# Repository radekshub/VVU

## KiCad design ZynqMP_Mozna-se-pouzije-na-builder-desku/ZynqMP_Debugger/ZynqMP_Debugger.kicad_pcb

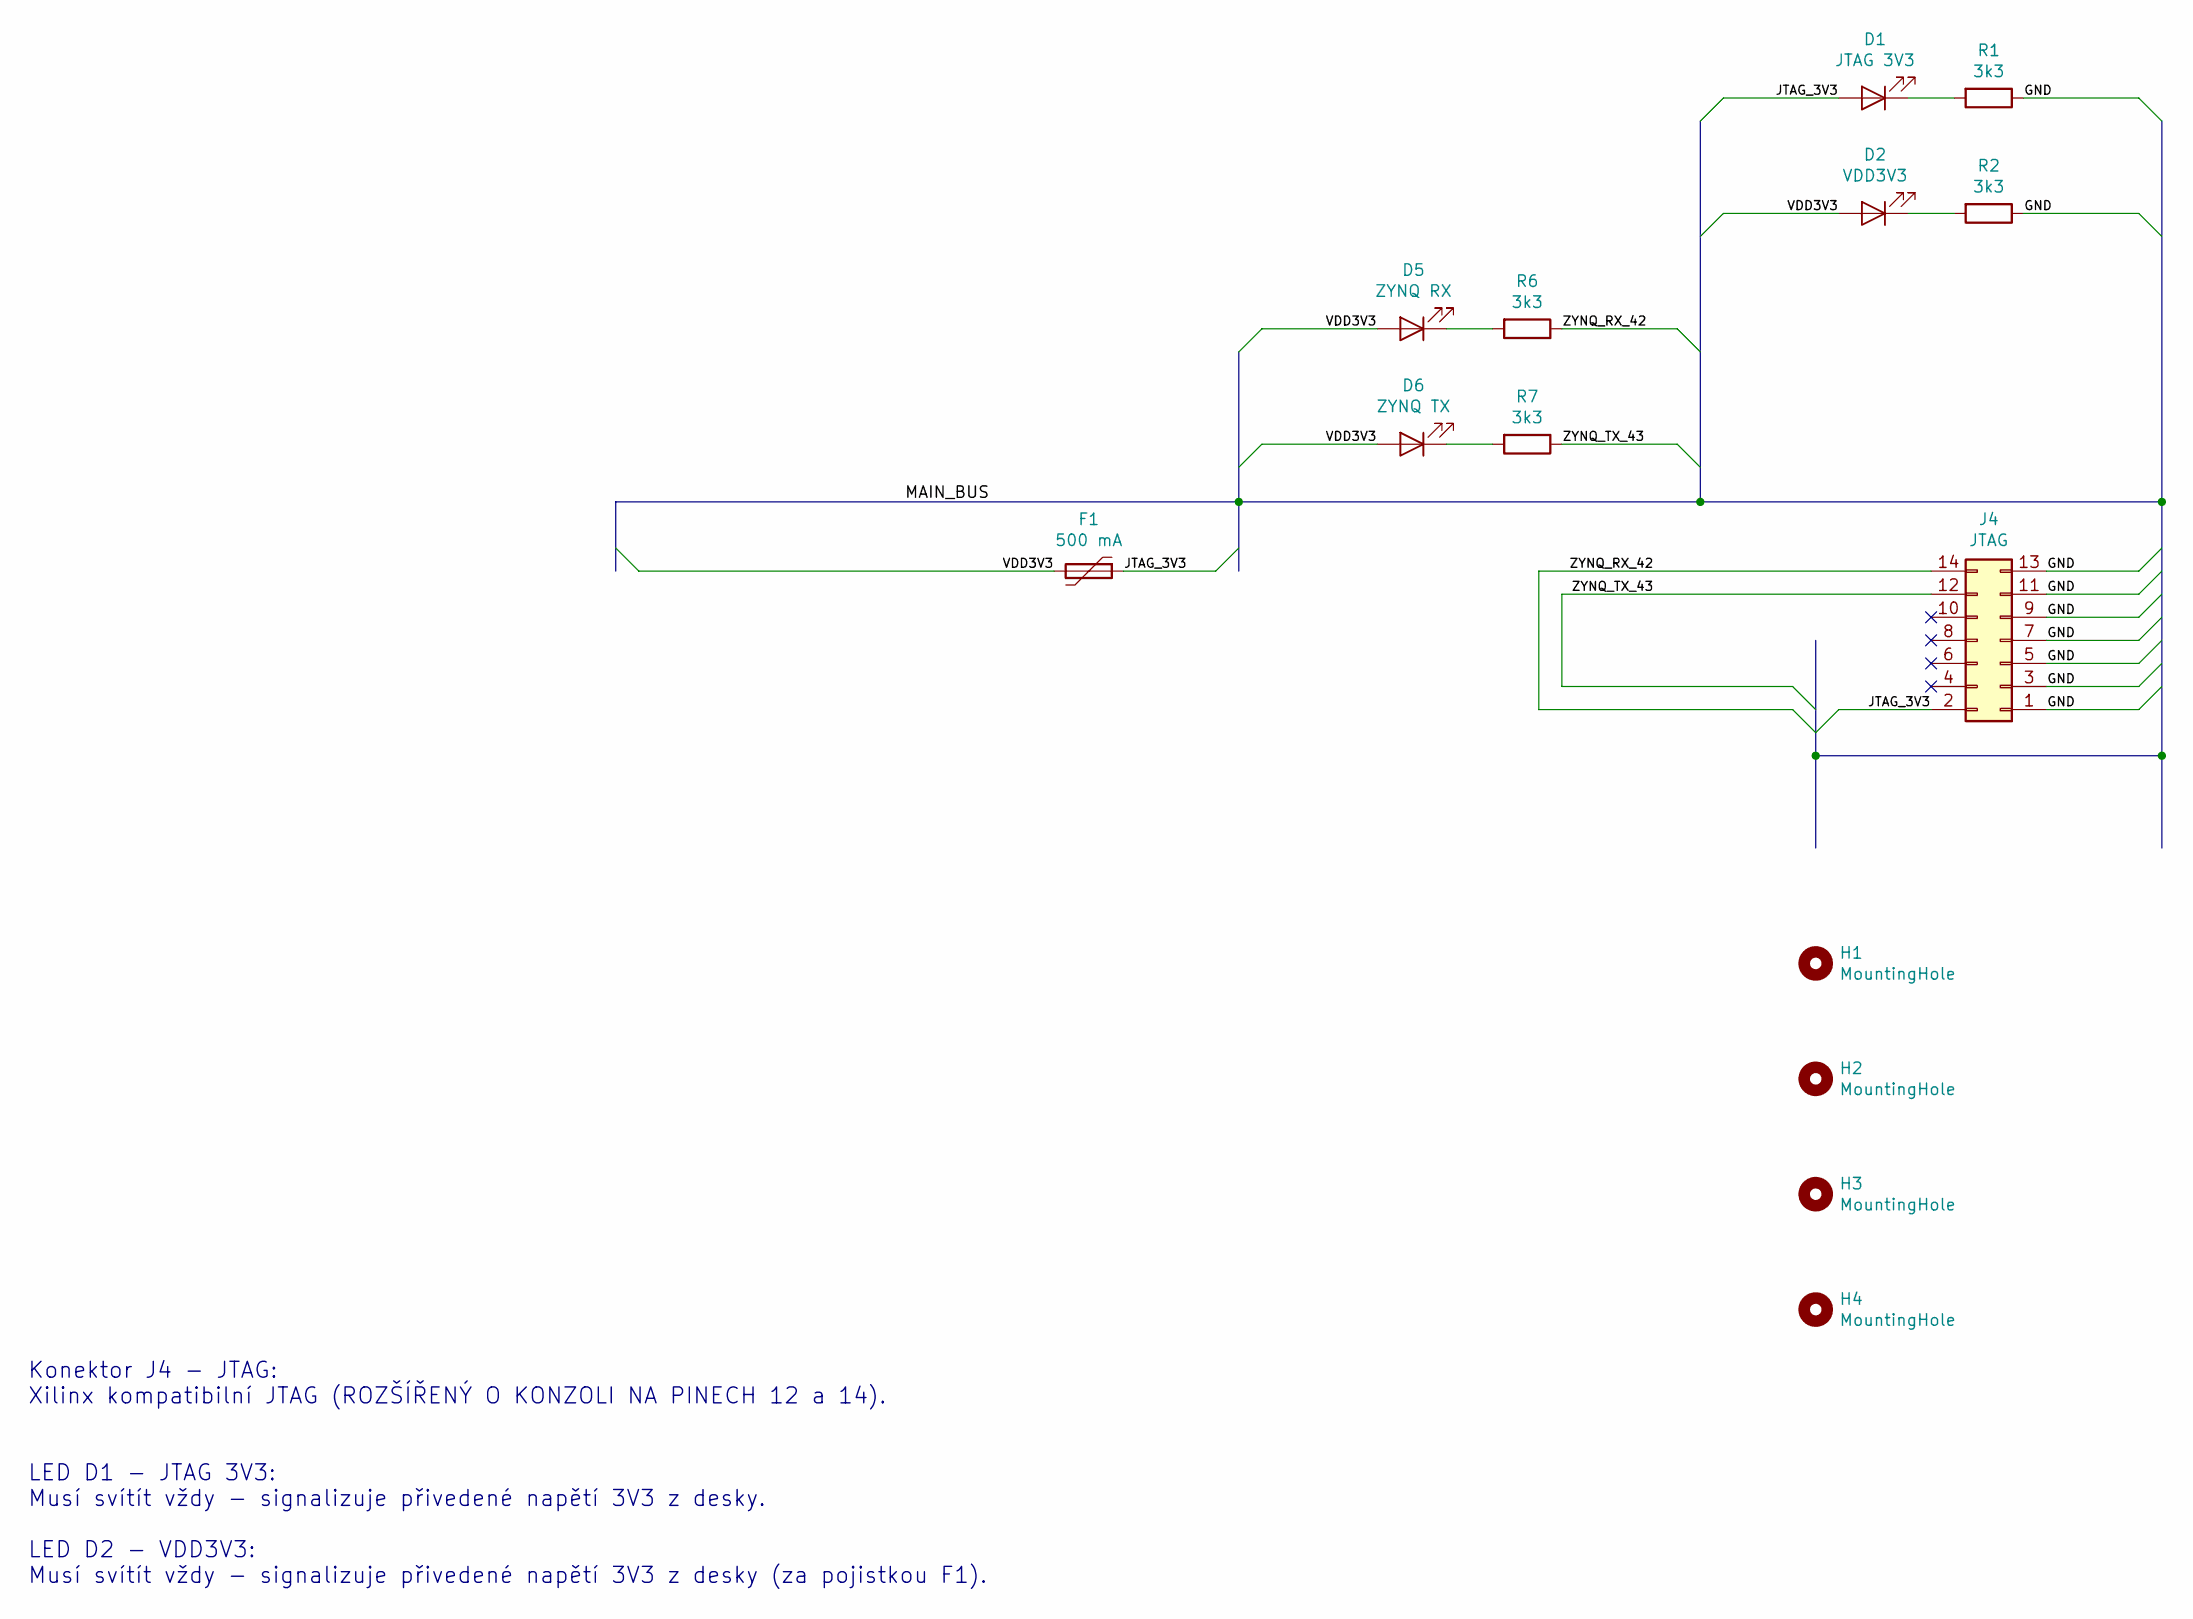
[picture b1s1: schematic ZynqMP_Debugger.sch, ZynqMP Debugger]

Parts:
D1: JTAG 3V3; LED_0805_2012Metric_Pad1.15x1.40mm_HandSolder
D2: VDD3V3; LED_0805_2012Metric_Pad1.15x1.40mm_HandSolder
D5: ZYNQ RX; LED_0805_2012Metric_Pad1.15x1.40mm_HandSolder
D6: ZYNQ TX; LED_0805_2012Metric_Pad1.15x1.40mm_HandSolder
F1: 500 mA; Fuse_1206_3216Metric_Pad1.42x1.75mm_HandSolder
H1, H2, H3, H4: MountingHole; MountingHole_4.3mm_M4_Pad_Via
J4: JTAG; JST_PHD_B14B-PHDSS_2x07_P2.00mm_Vertical
R1, R2, R6, R7: 3k3; R_0805_2012Metric_Pad1.15x1.40mm_HandSolder

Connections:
/GND: J4.1, J4.3, J4.5, J4.7, J4.9, J4.11, J4.13, R1.1, R2.1
/JTAG_3V3: D1.2 (A), F1.1, J4.2
/VDD3V3: D2.2 (A), D5.2 (A), D6.2 (A), F1.2
/ZYNQ_RX_42: J4.14, R6.1
/ZYNQ_TX_43: J4.12, R7.1
unnamed: D1.1 (K), R1.2
unnamed: D2.1 (K), R2.2
unnamed: D5.1 (K), R6.2
unnamed: D6.1 (K), R7.2

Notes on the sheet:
Konektor J4 - JTAG: Xilinx kompatibilní JTAG (ROZŠÍŘENÝ O KONZOLI NA PINECH 12 a 14). LED D1 - JTAG 3V3: Musí svítít vždy - signalizuje přivedené napětí 3V3 z desky. LED D2 - VDD3V3: Musí svítít vždy - signalizuje přivedené napětí 3V3 z desky (za pojistkou F1).

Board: 2 copper layers, 14 parts (0 on the bottom side), 9 nets, no tracks yet.

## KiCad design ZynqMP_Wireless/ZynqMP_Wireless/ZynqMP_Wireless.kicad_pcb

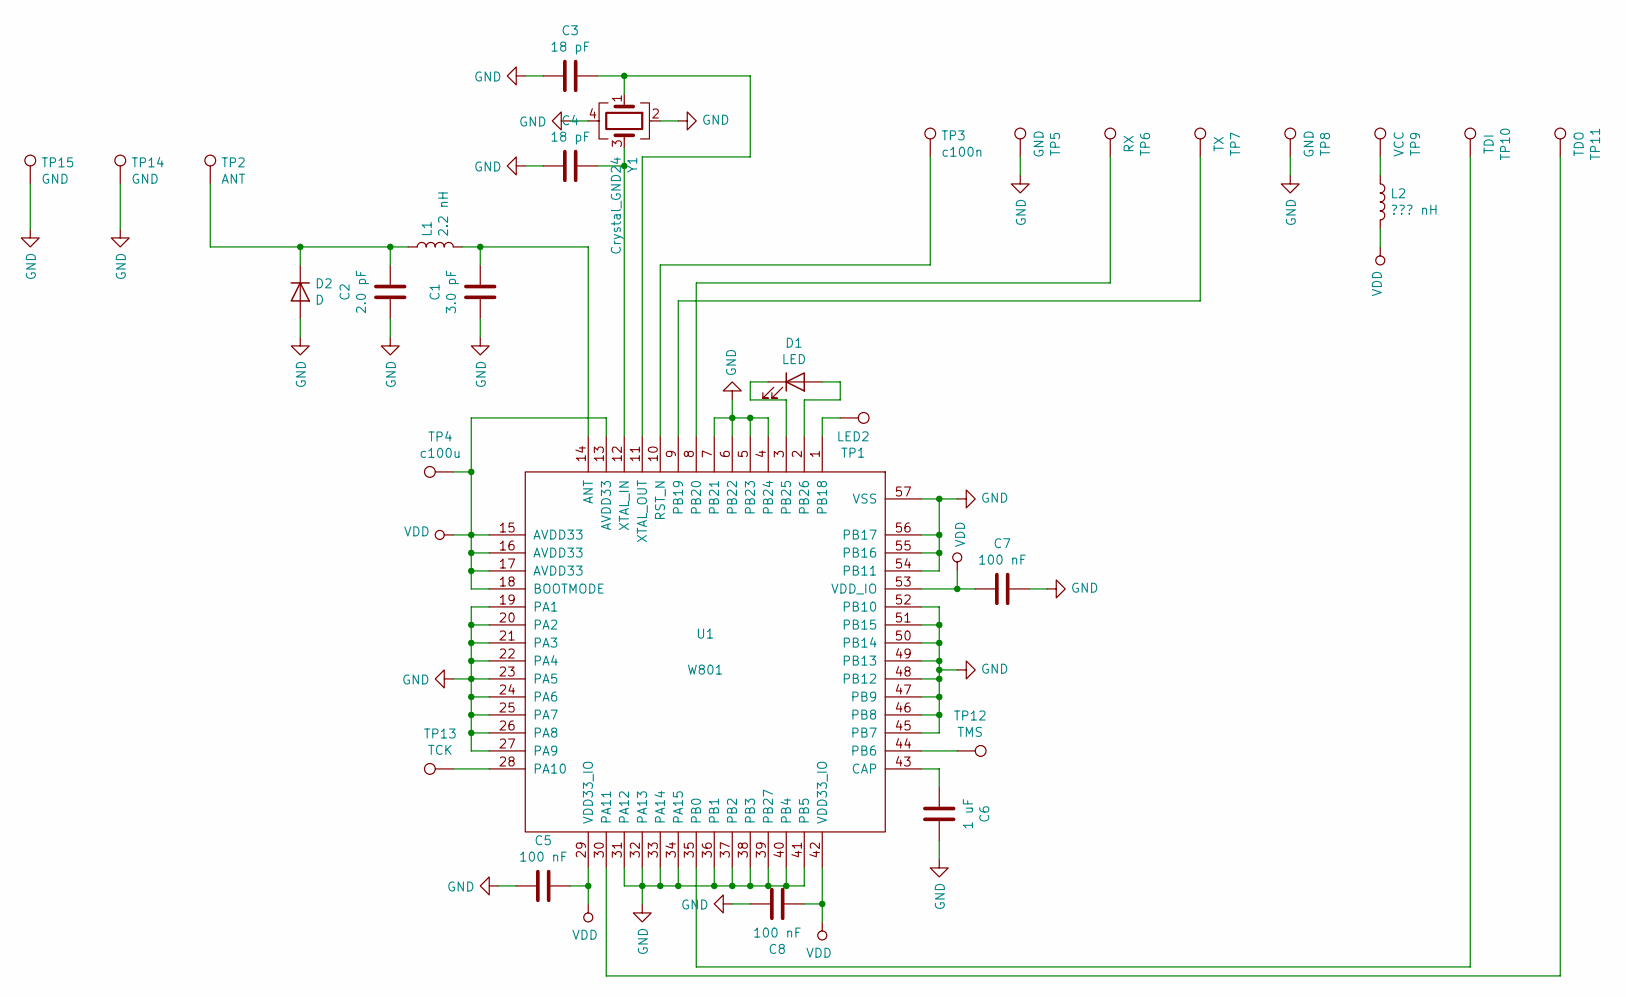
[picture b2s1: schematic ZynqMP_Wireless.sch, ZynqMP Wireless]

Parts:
C1: 3.0 pF; C_0201_0603Metric
C2: 2.0 pF; C_0201_0603Metric
C3, C4: 18 pF; C_0603_1608Metric
C5: 100 nF; C_0603_1608Metric_Pad1.05x0.95mm_HandSolder
C6: 1 uF; C_0603_1608Metric_Pad1.05x0.95mm_HandSolder
C7, C8: 100 nF; C_0603_1608Metric
D1: LED; LED_0603_1608Metric_Pad1.05x0.95mm_HandSolder
D2: D; D_0201_0603Metric
L1: 2.2 nH; L_0201_0603Metric
L2: ??? nH; L_0603_1608Metric_Pad1.05x0.95mm_HandSolder
TP1: LED2; TestPoint_Pad_1.0x1.0mm
TP2: ANT; MountingHole_4.3x6.2mm_M4_Pad
TP3: c100n; TestPoint_Pad_1.0x1.0mm
TP4: c100u; TestPoint_Pad_1.0x1.0mm
TP5, TP8: GND; TestPoint_Pad_1.0x1.0mm
TP6: RX; TestPoint_Pad_1.0x1.0mm
TP7: TX; TestPoint_Pad_1.0x1.0mm
TP9: VCC; TestPoint_Pad_1.0x1.0mm
TP10: TDI; TestPoint_Pad_1.0x1.0mm
TP11: TDO; TestPoint_Pad_1.0x1.0mm
TP12: TMS; TestPoint_Pad_1.0x1.0mm
TP13: TCK; TestPoint_Pad_1.0x1.0mm
TP14, TP15: GND; MountingHole_4.3x6.2mm_M4_Pad
U1: W801
Y1: Crystal_GND24; Crystal_SMD_3225-4Pin_3.2x2.5mm

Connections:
GND: C1.2, C2.2, C3.2, C4.2, C5.2, C6.1, C7.1, C8.1, D2.2 (A), TP5.1, TP8.1, TP14.1, TP15.1, U1.4 (PB24), U1.5 (PB23), U1.6 (PB22), U1.7 (PB21), U1.19 (PA1), U1.20 (PA2), U1.21 (PA3), U1.22 (PA4), U1.23 (PA5), U1.24 (PA6), U1.25 (PA7), U1.26 (PA8), U1.27 (PA9), U1.31 (PA12), U1.32 (PA13), U1.33 (PA14), U1.34 (PA15), U1.36 (PB1), U1.37 (PB2), U1.38 (PB3), U1.39 (PB27), U1.40 (PB4), U1.41 (PB5), U1.45 (PB7), U1.46 (PB8), U1.47 (PB9), U1.48 (PB12), U1.49 (PB13), U1.50 (PB14), U1.51 (PB15), U1.52 (PB10), U1.54 (PB11), U1.55 (PB16), U1.56 (PB17), U1.57 (VSS), Y1.2, Y1.4
unnamed: C1.1, L1.2, U1.14 (ANT)
unnamed: C2.1, D2.1 (K), L1.1, TP2.1
unnamed: C3.1, U1.11 (XTAL_OUT), Y1.1
unnamed: C4.1, U1.12 (XTAL_IN), Y1.3
unnamed: C6.2, U1.43 (CAP)
unnamed: D1.1 (K), U1.3 (PB25)
unnamed: D1.2 (A), U1.2 (PB26)
unnamed: L2.1, TP9.1
unnamed: TP1.1, U1.1 (PB18)
unnamed: TP3.1, U1.10 (RST_N)
unnamed: TP6.1, U1.8 (PB20)
unnamed: TP7.1, U1.9 (PB19)
unnamed: TP10.1, U1.35 (PB0)
unnamed: TP11.1, U1.30 (PA11)
unnamed: TP12.1, U1.44 (PB6)
unnamed: TP13.1, U1.28 (PA10)
VDD: C5.1, C7.2, C8.2, L2.2, TP4.1, U1.13 (AVDD33), U1.15 (AVDD33), U1.16 (AVDD33), U1.17 (AVDD33), U1.18 (BOOTMODE), U1.29 (VDD33_IO), U1.42 (VDD33_IO), U1.53 (VDD_IO)

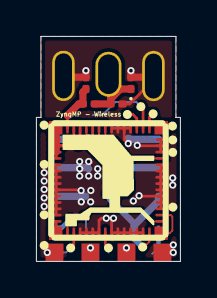
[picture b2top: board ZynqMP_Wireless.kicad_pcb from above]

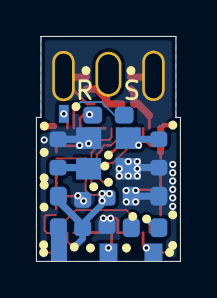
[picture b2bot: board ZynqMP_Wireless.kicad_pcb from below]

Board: 4 copper layers, 8.0 x 12.5 mm, 29 parts (13 on the bottom side), 18 nets.

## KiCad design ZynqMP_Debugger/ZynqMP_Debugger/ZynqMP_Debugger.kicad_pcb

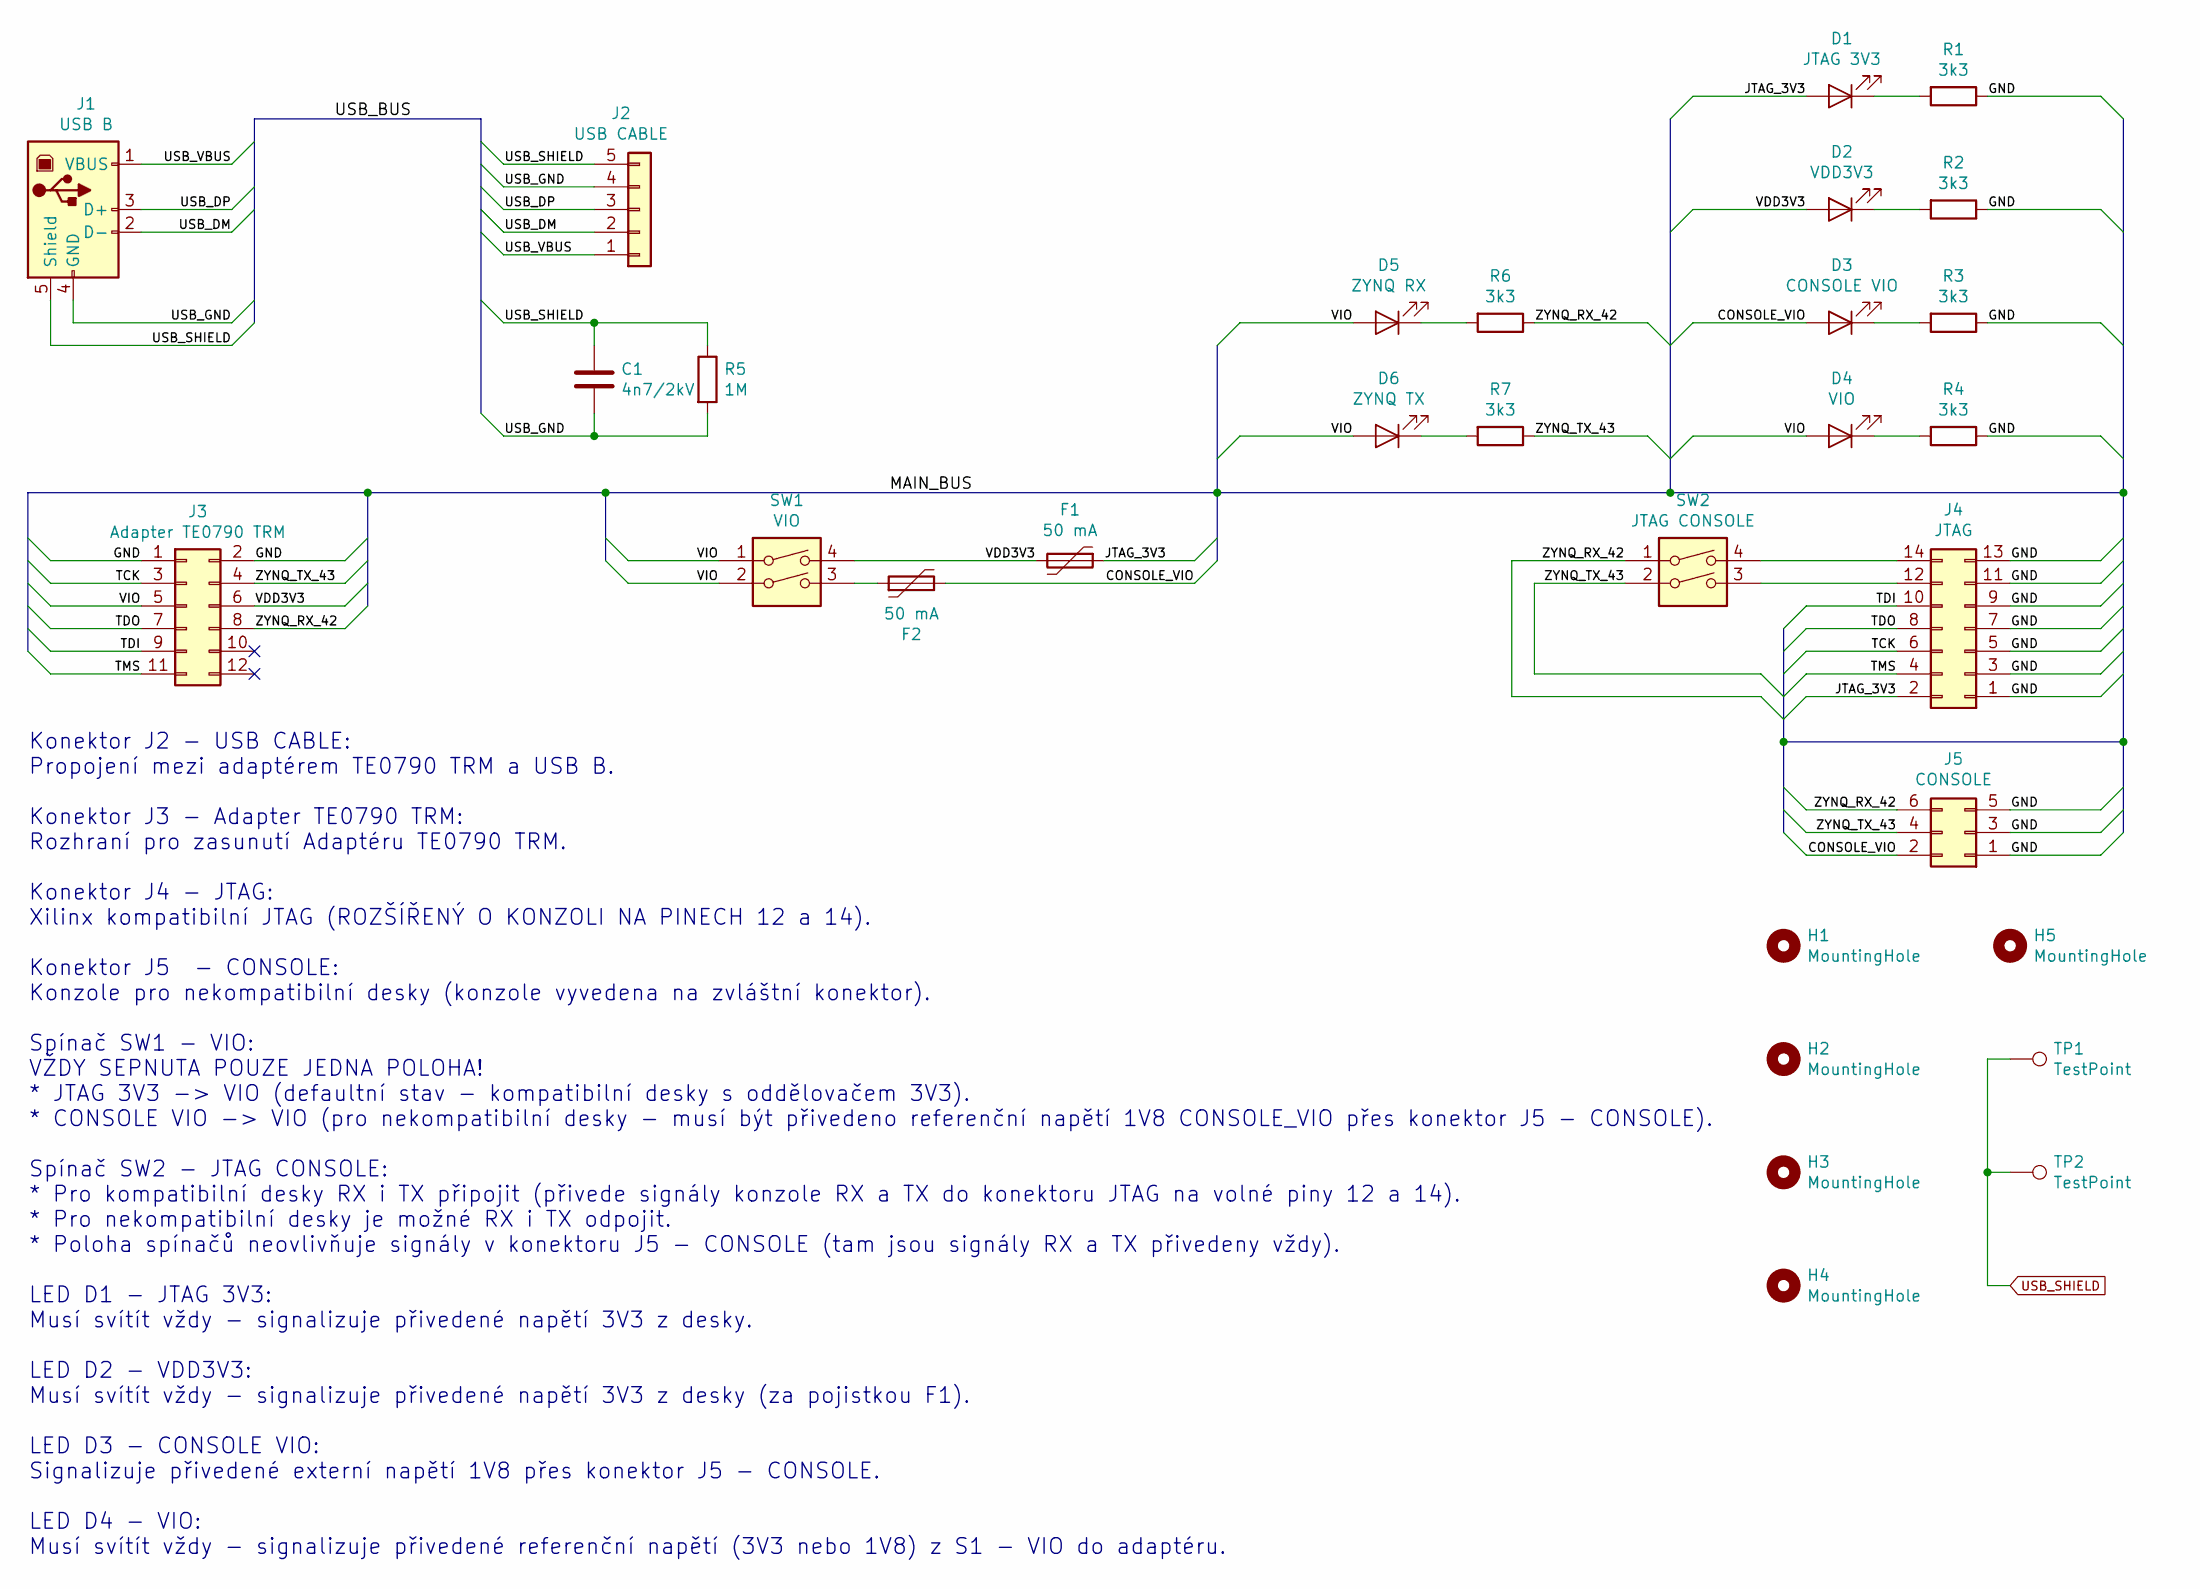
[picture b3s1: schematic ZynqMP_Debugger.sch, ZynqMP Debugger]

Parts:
C1: 4n7/2kV; C_Disc_D7.5mm_W2.5mm_P5.00mm
D1: JTAG 3V3; LED_0805_2012Metric_Pad1.15x1.40mm_HandSolder
D2: VDD3V3; LED_0805_2012Metric_Pad1.15x1.40mm_HandSolder
D3: CONSOLE VIO; LED_0805_2012Metric_Pad1.15x1.40mm_HandSolder
D4: VIO; LED_0805_2012Metric_Pad1.15x1.40mm_HandSolder
D5: ZYNQ RX; LED_0805_2012Metric_Pad1.15x1.40mm_HandSolder
D6: ZYNQ TX; LED_0805_2012Metric_Pad1.15x1.40mm_HandSolder
F1, F2: 50 mA; Fuse_1206_3216Metric_Pad1.42x1.75mm_HandSolder
H1, H2, H3, H4: MountingHole; MountingHole_4.3mm_M4_Pad_Via
H5: MountingHole; MountingHole_3mm_Pad_Via
J1: USB B; USB_B_OST_USB-B1HSxx_Horizontal
J2: USB CABLE; PinHeader_1x05_P2.54mm_Horizontal
J3: Adapter TE0790 TRM; PinHeader_2x06_P2.54mm_Vertical
J4: JTAG; JST_PHD_B14B-PHDSS_2x07_P2.00mm_Vertical
J5: CONSOLE; IDC-Header_2x03_P2.54mm_Vertical
R1, R2, R3, R4, R6, R7: 3k3; R_0805_2012Metric_Pad1.15x1.40mm_HandSolder
R5: 1M; R_0805_2012Metric_Pad1.15x1.40mm_HandSolder
SW1: VIO; SW_DIP_SPSTx02_Slide_9.78x7.26mm_W7.62mm_P2.54mm
SW2: JTAG CONSOLE; SW_DIP_SPSTx02_Slide_9.78x7.26mm_W7.62mm_P2.54mm
TP1, TP2: TestPoint; TestPoint_Bridge_Pitch5.08mm_Drill1.3mm

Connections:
/CONSOLE_VIO: D3.2 (A), F2.2, J5.2
/GND: J3.1, J3.2, J4.1, J4.3, J4.5, J4.7, J4.9, J4.11, J4.13, J5.1, J5.3, J5.5, R1.1, R2.1, R3.1, R4.1
/JTAG_3V3: D1.2 (A), F1.1, J4.2
/TCK: J3.3, J4.6
/TDI: J3.9, J4.10
/TDO: J3.7, J4.8
/TMS: J3.11, J4.4
/USB_DM: J1.2 (D-), J2.2
/USB_DP: J1.3 (D+), J2.3
/USB_GND: C1.2, J1.4 (GND), J2.4, R5.2
/USB_VBUS: J1.1 (VBUS), J2.1
/VDD3V3: D2.2 (A), F1.2, J3.6, SW1.4
/VIO: D4.2 (A), D5.2 (A), D6.2 (A), J3.5, SW1.1, SW1.2
/ZYNQ_RX_42: J3.8, J5.6, R6.1, SW2.1
/ZYNQ_TX_43: J3.4, J5.4, R7.1, SW2.2
unnamed: D1.1 (K), R1.2
unnamed: D2.1 (K), R2.2
unnamed: D3.1 (K), R3.2
unnamed: D4.1 (K), R4.2
unnamed: D5.1 (K), R6.2
unnamed: D6.1 (K), R7.2
unnamed: F2.1, SW1.3
unnamed: J4.12, SW2.3
unnamed: J4.14, SW2.4
USB_SHIELD: C1.1, J1.5 (Shield), J2.5, R5.1, TP1.1, TP2.1

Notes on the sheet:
Konektor J2 - USB CABLE: Propojení mezi adaptérem TE0790 TRM a USB B. Konektor J3 - Adapter TE0790 TRM: Rozhraní pro zasunutí Adaptéru TE0790 TRM. Konektor J4 - JTAG: Xilinx kompatibilní JTAG (ROZŠÍŘENÝ O KONZOLI NA PINECH 12 a 14). Konektor J5 - CONSOLE: Konzole pro nekompatibilní desky (konzole v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

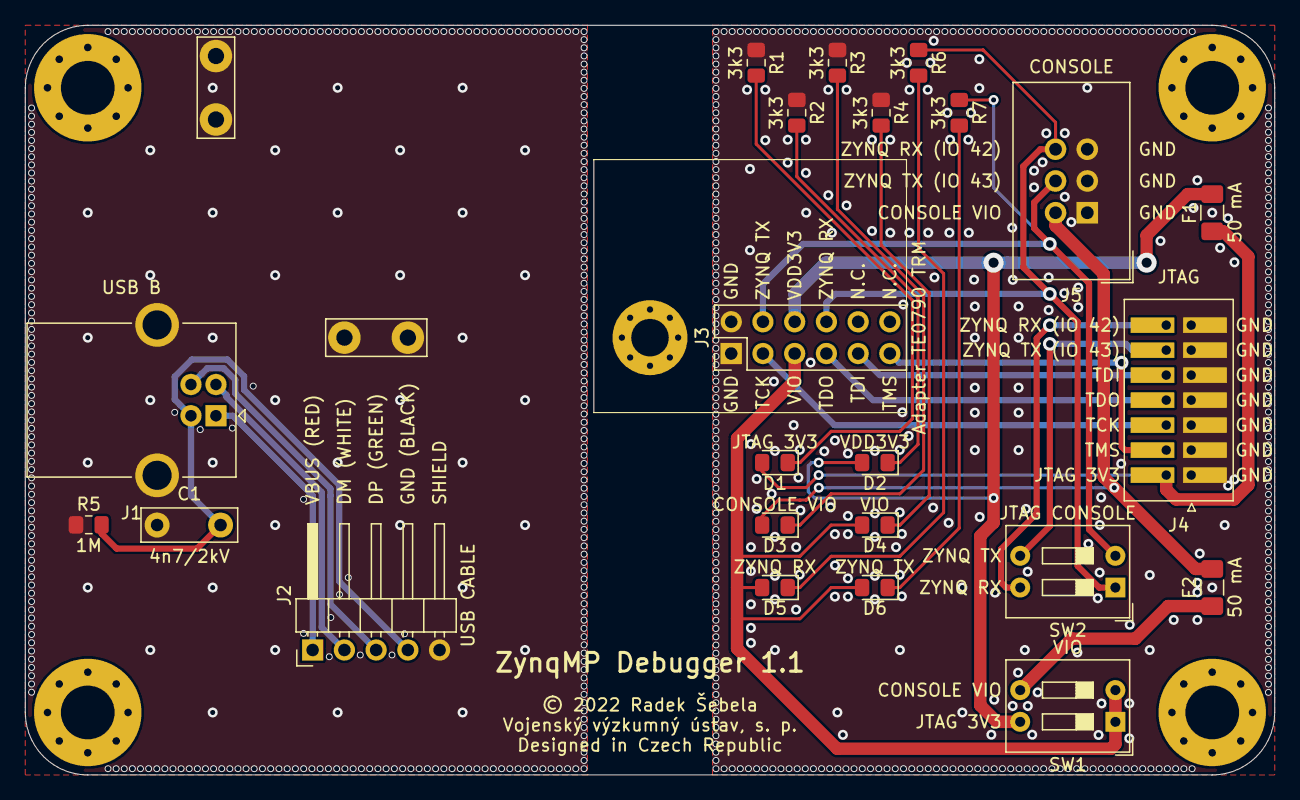
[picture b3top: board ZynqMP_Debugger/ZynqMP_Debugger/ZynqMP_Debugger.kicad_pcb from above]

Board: 2 copper layers, 100.0 x 60.0 mm, 30 parts (0 on the bottom side), 25 nets.

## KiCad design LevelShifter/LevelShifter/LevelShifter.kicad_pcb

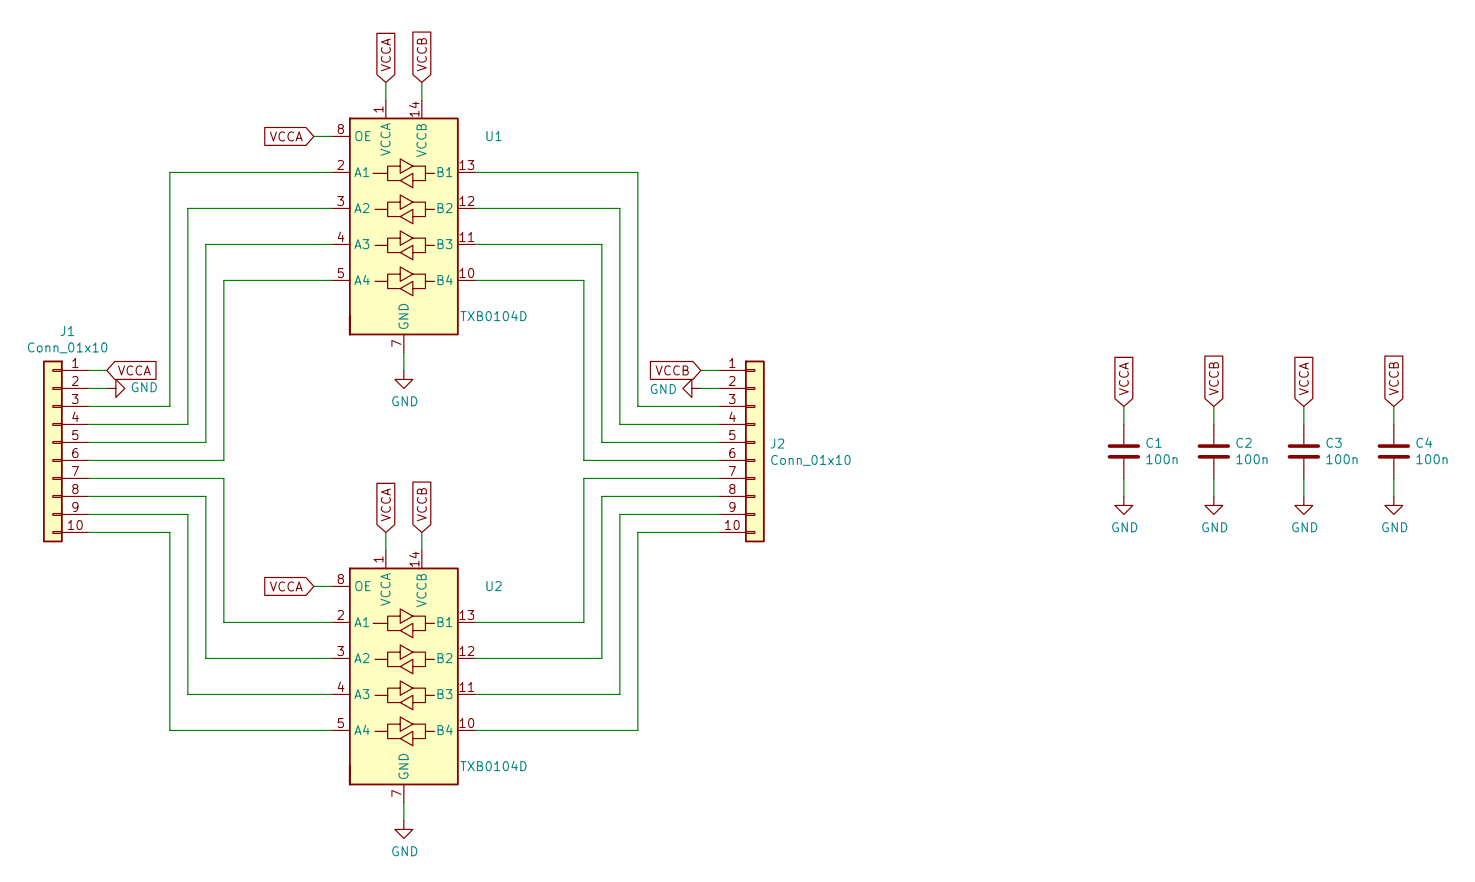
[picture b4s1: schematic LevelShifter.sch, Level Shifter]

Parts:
C1, C2, C3, C4: 100n; C_0805_2012Metric_Pad1.15x1.40mm_HandSolder
J1, J2: Conn_01x10; PinHeader_1x10_P2.00mm_Vertical
U1, U2: TXB0104D; SOIC-14_3.9x8.7mm_P1.27mm

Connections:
GND: C1.2, C2.2, C3.2, C4.2, J1.2, J2.2, U1.7 (GND), U2.7 (GND)
unnamed: J1.3, U1.2 (A1)
unnamed: J1.4, U1.3 (A2)
unnamed: J1.5, U1.4 (A3)
unnamed: J1.6, U1.5 (A4)
unnamed: J1.7, U2.2 (A1)
unnamed: J1.8, U2.3 (A2)
unnamed: J1.9, U2.4 (A3)
unnamed: J1.10, U2.5 (A4)
unnamed: J2.3, U1.13 (B1)
unnamed: J2.4, U1.12 (B2)
unnamed: J2.5, U1.11 (B3)
unnamed: J2.6, U1.10 (B4)
unnamed: J2.7, U2.13 (B1)
unnamed: J2.8, U2.12 (B2)
unnamed: J2.9, U2.11 (B3)
unnamed: J2.10, U2.10 (B4)
VCCA: C1.1, C3.1, J1.1, U1.1 (VCCA), U1.8 (OE), U2.1 (VCCA), U2.8 (OE)
VCCB: C2.1, C4.1, J2.1, U1.14 (VCCB), U2.14 (VCCB)

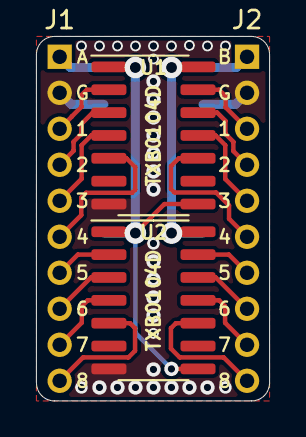
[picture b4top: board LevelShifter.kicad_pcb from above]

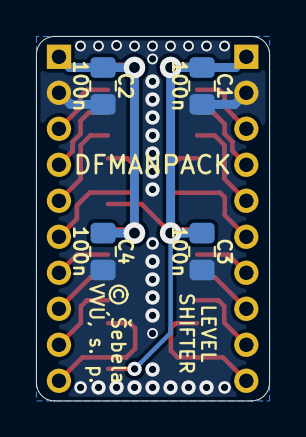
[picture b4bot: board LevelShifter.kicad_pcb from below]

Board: 2 copper layers, 13.0 x 20.2 mm, 8 parts (4 on the bottom side), 19 nets.

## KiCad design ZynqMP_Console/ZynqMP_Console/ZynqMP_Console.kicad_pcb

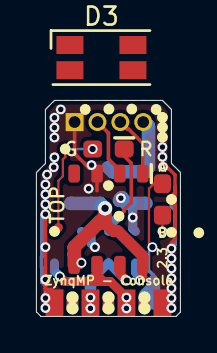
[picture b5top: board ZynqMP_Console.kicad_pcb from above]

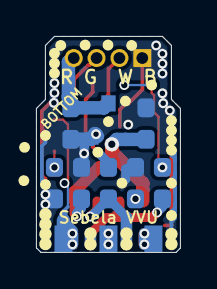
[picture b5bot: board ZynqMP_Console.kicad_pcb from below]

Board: 2 copper layers, 8.0 x 12.0 mm, 20 parts (11 on the bottom side), 11 nets.

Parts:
C1, C2: 1u; C_0603_1608Metric_Pad1.05x0.95mm_HandSolder
C3, C4: 100n; C_0603_1608Metric_Pad1.05x0.95mm_HandSolder
D1, D2: LED; LED_0603_1608Metric_Pad1.05x0.95mm_HandSolder
D3: LED_RGBA; LED_RGB_1210
J1: Conn_01x04; PinHeader_1x04_P1.27mm_Vertical
R1, R2: 330; R_0603_1608Metric_Pad1.05x0.95mm_HandSolder
R3: 1k2; R_0603_1608Metric_Pad1.05x0.95mm_HandSolder
TP1: VCC; TestPoint_Pad_1.0x1.0mm
TP2: ZTX; TestPoint_Pad_1.0x1.0mm
TP3: ZRX; TestPoint_Pad_1.0x1.0mm
TP4, TP5: GND; TestPoint_Pad_1.0x1.0mm
TP6: TDI; TestPoint_Pad_1.0x1.0mm
TP7: TDO; TestPoint_Pad_1.0x1.0mm
U1: CH340N; SOP-8_3.76x4.96mm_P1.27mm
U2: XC6206PxxxMR; SOT-23

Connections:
/RGB_A: D2.2, TP1.1
/RGB_B: D2.1, R3.1
/RGB_G: D1.1, R1.2
/RGB_R: D1.2, R2.2
GND: C1.2, C2.2, C3.2, C4.2, J1.1, R3.2, TP4.1, TP5.1, U1.3, U2.1
unnamed: C1.1, J1.4, U2.3
unnamed: C2.1, C3.1, C4.1, U1.5, U1.8, U2.2
unnamed: J1.2, U1.2
unnamed: J1.3, U1.1
unnamed: R1.1, TP3.1, U1.6
unnamed: R2.1, TP2.1, U1.7

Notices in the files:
ZynqMP_Debugger/ZynqMP_Debugger/ZynqMP_Debugger.kicad_pcb:
© 2022 Radek Šebela
ZynqMP_Mozna-se-pouzije-na-builder-desku/ZynqMP_Debugger/ZynqMP_Debugger.kicad_pcb:
© 2023 Radek Šebela
